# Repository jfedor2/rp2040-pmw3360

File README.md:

# RP2040+PMW3360

This repository contains design files and code for a PCB carrying Raspberry Pi's RP2040 chip and the PixArt PMW3360 optical mouse sensor. They can be used for rapid prototyping of USB mice and trackballs.

The files in the [fabrication](fabrication) folder can be used to order this board from JLCPCB with SMT assembly. The board you get includes everything except the sensor. If some of the specific components are out of stock, try to find an equivalent with the same package and parameters.

The sensor chip should be soldered on the bottom side (the opposite side from all the other components). The dot marks pin 1. The optic goes on the top side.

If you're looking for a convenient way of mounting mouse button switches in a case, perhaps [this repository](https://github.com/jfedor2/mouse-switch-mount-pcb) will be of use.

Examples of devices made using this board:

* [Trackball 7](https://www.prusaprinters.org/prints/83631-trackball-7)
* [Trackball 8](https://www.prusaprinters.org/prints/84148-trackball-8)
* [Spherical trackball](https://www.prusaprinters.org/prints/85053-spherical-trackball)
* [Two-ball trackball](https://github.com/jfedor2/two-ball-trackball)
* [Mouse 1](https://www.prusaprinters.org/prints/87379-mouse-1)
* [Mouse 2](https://www.prusaprinters.org/prints/88403-mouse-2)
* [Trackball with twist-to-scroll](https://github.com/jfedor2/twist-to-scroll-trackball)
* [Trackball with scroll ring](https://github.com/jfedor2/scroll-ring-trackball)
* [Mouse 4](https://www.prusaprinters.org/prints/127451-mouse-4)
* [Trackball 15](https://www.prusaprinters.org/prints/131450-trackball-15), [15b/c](https://www.printables.com/model/263616-trackball-15bc), [15d/e](https://www.printables.com/model/267954-trackball-15de)

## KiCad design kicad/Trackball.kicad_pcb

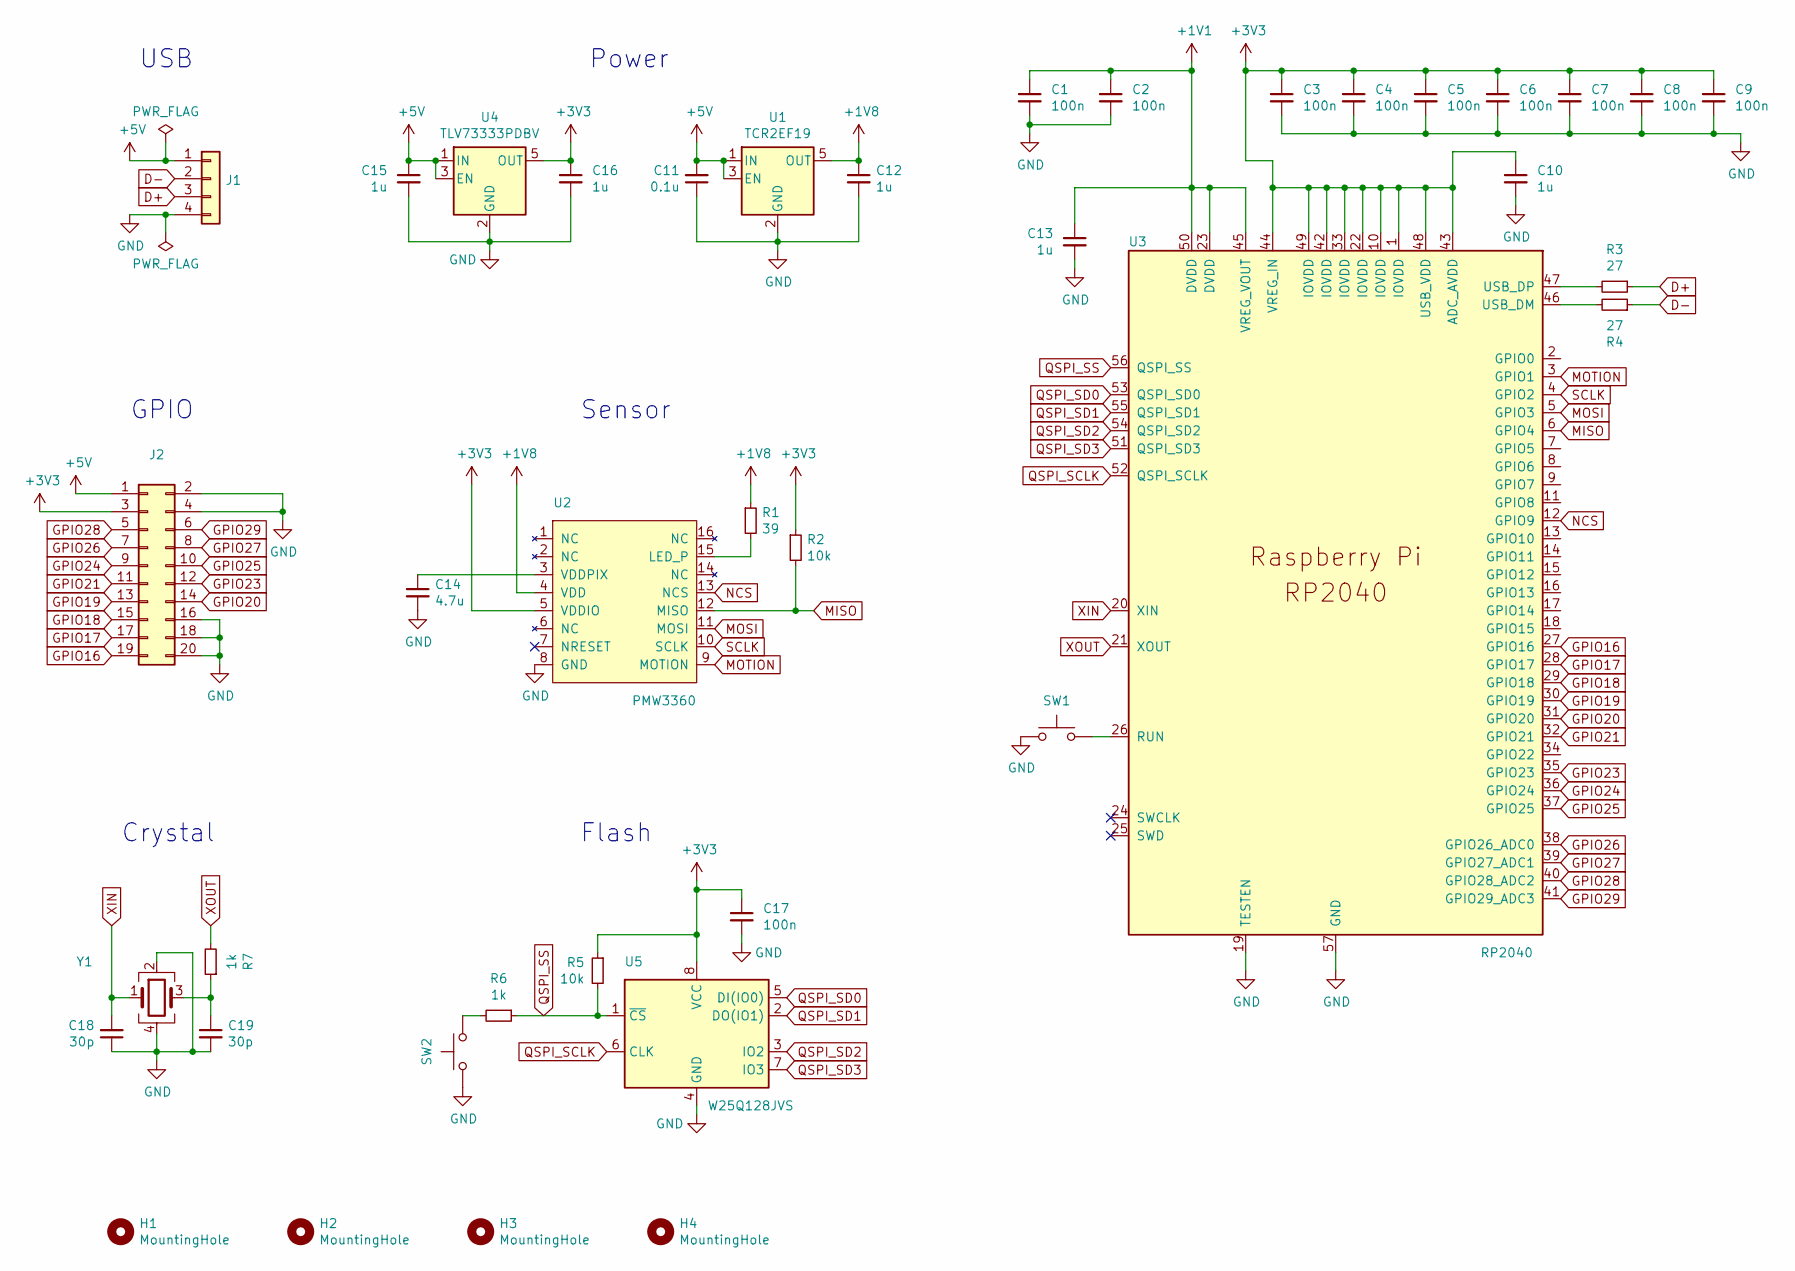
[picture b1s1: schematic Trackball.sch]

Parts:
C1, C2, C3, C4, C5, C6, C7, C8, C9, C17: 100n; C_0402_1005Metric; LCSC C1525
C10, C13, C15, C16: 1u; C_0402_1005Metric; LCSC C52923
C11: 0.1u; C_0603_1608Metric; LCSC C14663
C12: 1u; C_0603_1608Metric; LCSC C15849
C14: 4.7u; C_0402_1005Metric; LCSC C23733
C18, C19: 30p; C_0402_1005Metric; LCSC C1570
H1, H2, H3, H4: MountingHole; MountingHole_3.2mm_M3
J1: Conn_01x04; PinHeader_1x04_P2.54mm_Vertical
J2: Conn_02x10_Odd_Even; PinHeader_2x10_P2.54mm_Vertical
R1: 39; R_0402_1005Metric; LCSC C25110
R2, R5: 10k; R_0402_1005Metric; LCSC C25744
R3, R4: 27; R_0402_1005Metric; LCSC C138021
R6, R7: 1k; R_0402_1005Metric; LCSC C11702
SW1, SW2: SW_Push; SW_SPST_Omron_B3FS-100xP; LCSC C271750
U1: TCR2EF19; SOT-23-5; LCSC C146366
U2: PMW3360
U3: RP2040; RP2040-QFN-56; LCSC C2040
U4: TLV73333PDBV; SOT-23-5; LCSC C134139
U5: W25Q128JVS; SOIC-8_5.23x5.23mm_P1.27mm; LCSC C97521
Y1: Crystal_GND24; Crystal_SMD_3225-4Pin_3.2x2.5mm; LCSC C9002

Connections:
+1V1: C1.1, C2.1, C13.1, U3.23 (DVDD), U3.45 (VREG_VOUT), U3.50 (DVDD)
+1V8: C12.1, R1.1, U1.5 (OUT), U2.4 (VDD)
+3V3: C3.1, C4.1, C5.1, C6.1, C7.1, C8.1, C9.1, C10.1, C16.1, C17.1, J2.3, R2.1, R5.1, U2.5 (VDDIO), U3.1 (IOVDD), U3.10 (IOVDD), U3.22 (IOVDD), U3.33 (IOVDD), U3.42 (IOVDD), U3.43 (ADC_AVDD), U3.44 (VREG_IN), U3.48 (USB_VDD), U3.49 (IOVDD), U4.5 (OUT), U5.8 (VCC)
+5V: C11.2, C15.1, J1.1, J2.1, U1.1 (IN), U1.3 (EN), U4.1 (IN), U4.3 (EN)
D+: J1.3, R3.1
D-: J1.2, R4.1
GND: C1.2, C2.2, C3.2, C4.2, C5.2, C6.2, C7.2, C8.2, C9.2, C10.2, C11.1, C12.2, C13.2, C14.2, C15.2, C16.2, C17.2, C18.1, C19.2, J1.4, J2.2, J2.4, J2.16, J2.18, J2.20, SW1.1, SW2.1, U1.2 (GND), U2.8 (GND), U3.19 (TESTEN), U3.57 (GND), U4.2 (GND), U5.4 (GND), Y1.2, Y1.4
GPIO16: J2.19, U3.27 (GPIO16)
GPIO17: J2.17, U3.28 (GPIO17)
GPIO18: J2.15, U3.29 (GPIO18)
GPIO19: J2.13, U3.30 (GPIO19)
GPIO20: J2.14, U3.31 (GPIO20)
GPIO21: J2.11, U3.32 (GPIO21)
GPIO23: J2.12, U3.35 (GPIO23)
GPIO24: J2.9, U3.36 (GPIO24)
GPIO25: J2.10, U3.37 (GPIO25)
GPIO26: J2.7, U3.38 (GPIO26_ADC0)
GPIO27: J2.8, U3.39 (GPIO27_ADC1)
GPIO28: J2.5, U3.40 (GPIO28_ADC2)
GPIO29: J2.6, U3.41 (GPIO29_ADC3)
MISO: R2.2, U2.12 (MISO), U3.6 (GPIO4)
MOSI: U2.11 (MOSI), U3.5 (GPIO3)
MOTION: U2.9 (MOTION), U3.3 (GPIO1)
NCS: U2.13 (NCS), U3.12 (GPIO9)
unnamed: C14.1, U2.3 (VDDPIX)
unnamed: C19.1, R7.1, Y1.3
unnamed: R1.2, U2.15 (LED_P)
unnamed: R3.2, U3.47 (USB_DP)
unnamed: R4.2, U3.46 (USB_DM)
unnamed: R6.2, SW2.2
unnamed: SW1.2, U3.26 (RUN)
QSPI_SCLK: U3.52 (QSPI_SCLK), U5.6 (CLK)
QSPI_SD0: U3.53 (QSPI_SD0), U5.5 (DI(IO0))
QSPI_SD1: U3.55 (QSPI_SD1), U5.2 (DO(IO1))
QSPI_SD2: U3.54 (QSPI_SD2), U5.3 (IO2)
QSPI_SD3: U3.51 (QSPI_SD3), U5.7 (IO3)
QSPI_SS: R5.2, R6.1, U3.56 (QSPI_SS), U5.1 (~CS)
SCLK: U2.10 (SCLK), U3.4 (GPIO2)
XIN: C18.2, U3.20 (XIN), Y1.1
XOUT: R7.2, U3.21 (XOUT)

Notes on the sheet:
Crystal
Power
USB
Flash
GPIO
Sensor

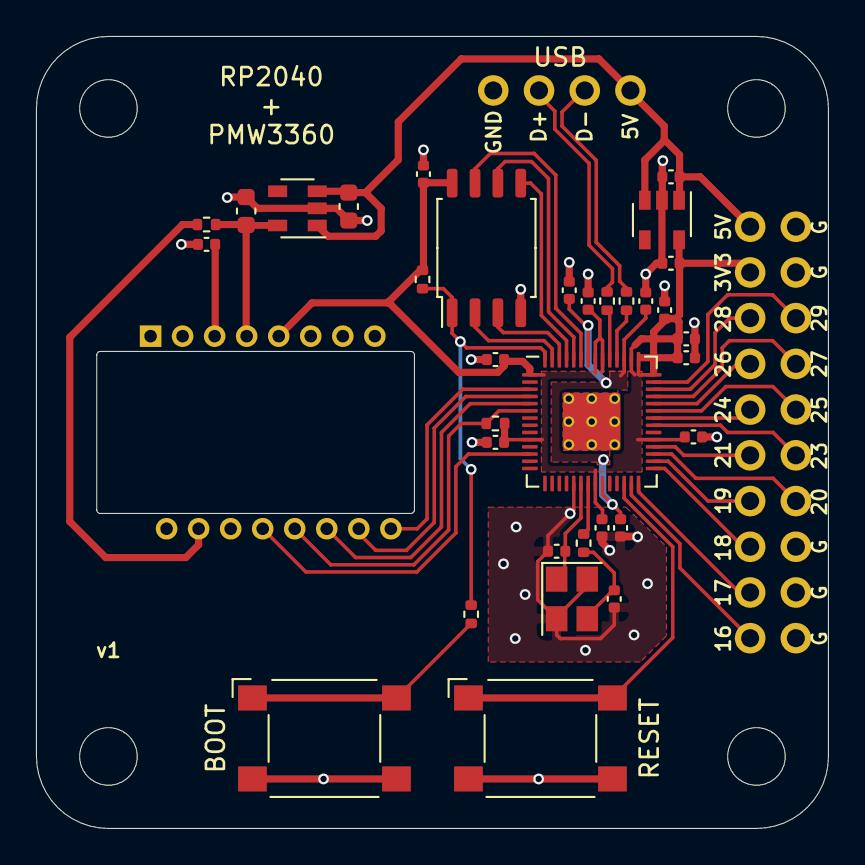
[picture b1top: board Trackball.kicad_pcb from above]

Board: 2 copper layers, 44.0 x 44.0 mm, 40 parts (1 on the bottom side), 40 nets.

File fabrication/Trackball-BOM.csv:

Comment,Designator,Footprint,LCSC
"0.1u","C11","Capacitor_SMD:C_0603_1608Metric","C14663"
"1u","C12","Capacitor_SMD:C_0603_1608Metric","C15849"
"4.7u","C14","Capacitor_SMD:C_0402_1005Metric","C23733"
"1u","C10,C13,C15,C16","Capacitor_SMD:C_0402_1005Metric","C52923"
"30p","C18,C19","Capacitor_SMD:C_0402_1005Metric","C1570"
"100n","C1,C2,C3,C4,C5,C6,C7,C8,C9,C17","Capacitor_SMD:C_0402_1005Metric","C1525"
"MountingHole","H1,H2,H3,H4","MountingHole:MountingHole_3.2mm_M3",""
"Conn_01x04","J1","Connector_PinHeader_2.54mm:PinHeader_1x04_P2.54mm_Vertical",""
"Conn_02x10_Odd_Even","J2","Connector_PinHeader_2.54mm:PinHeader_2x10_P2.54mm_Vertical",""
"39","R1","Resistor_SMD:R_0402_1005Metric","C25110"
"27","R3,R4","Resistor_SMD:R_0402_1005Metric","C138021"
"10k","R2,R5","Resistor_SMD:R_0402_1005Metric","C25744"
"1k","R6,R7","Resistor_SMD:R_0402_1005Metric","C11702"
"SW_Push","SW1,SW2","Button_Switch_SMD:SW_SPST_Omron_B3FS-100xP","C271750"
"TCR2EF19","U1","Package_TO_SOT_SMD:SOT-23-5","C146366"
"PMW3360","U2","PMW3360:PMW3360",""
"RP2040","U3","RP2040:RP2040-QFN-56","C2040"
"TLV73333PDBV","U4","Package_TO_SOT_SMD:SOT-23-5","C134139"
"W25Q128JVS","U5","Package_SO:SOIC-8_5.23x5.23mm_P1.27mm","C97521"
"Crystal_GND24","Y1","Crystal:Crystal_SMD_3225-4Pin_3.2x2.5mm","C9002"

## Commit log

2021-10-30 Add another example device
2021-11-03 One more example device
2021-11-17 Yet another example device
2021-11-19 And one more example device
2021-12-15 Add two more example devices
2022-01-14 Don't fetch sensor data if !tud_hid_ready()
    Moves the tud_hid_ready() check to the beginning of the hid_task()
    function, so that we don't drop sensor readings if USB is not ready.
    With this change, the sensor keeps accumulating the deltas until we're
    ready for them.
2022-01-31 Add another trackball to example devices
2022-01-31 Add another mouse to example devices
2022-02-08 Add one more trackball to the list
2022-08-28 Add more variants to example device list
